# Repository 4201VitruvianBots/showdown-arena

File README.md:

SoCal Showdown Arena 
============
A field management system built around Cheesy arena with some modifications to fit the SoCal Showdown use case.

## Key features

**For participants and spectators**

* Same network isolation and security as the official FIRST FMS
* No-lag realtime scoring
* Team stack lights and seven-segment display are replaced by an LCD screen, which shows team info before the match and
  realtime scoring and timer during the match
* Smooth-scrolling rankings display
* Direct publishing of schedule, results, and rankings to The Blue Alliance

**For scorekeepers and event staff**

* Runs on Windows, macOS, and Linux
* No install prerequisites
* No "pre-start" &ndash; hardware is configured automatically and in the background
* Flexible and quick match schedule generation
* Streamlined realtime score entry
* Reports, results, and logs can be viewed from any computer
* An arbitrary number of auxiliary displays can be set up using any computer with just a web browser, to show rankings,
  queueing, field status, etc.

## License

Teams may use Cheesy Arena freely for practice, scrimmages, and off-season events. See [LICENSE](LICENSE) for more
details.

## Installing

**From a pre-built release**

Download the [latest release](https://github.com/Team254/cheesy-arena/releases). Pre-built packages are available for
Linux, macOS (x64 and M1), and Windows.

On recent versions of macOS, you may be prevented from running an app from an unidentified developer;
see [these instructions](https://support.apple.com/guide/mac-help/open-a-mac-app-from-an-unidentified-developer-mh40616/mac)
on how to bypass the warning.

**From source**

1. Download [Go](https://golang.org/dl/) (version 1.22 or later required)
1. Clone this GitHub repository to a location of your choice
1. Navigate to the repository's directory in the terminal
1. Compile the code with `go build`
1. Run the `cheesy-arena` or `cheesy-arena.exe` binary
1. Navigate to http://localhost:8080 in your browser (Google Chrome recommended)

**IP address configuration**

When running Cheesy Arena on a playing field with robots, set the IP address of the computer running Cheesy Arena to
10.0.100.5. By a convention baked into the FRC Driver Station software, driver stations will broadcast their presence on
the network to this hardcoded address so that the FMS does not need to discover them by some other method.

When running Cheesy Arena without robots for testing or development, pass the `-dev` flag to bind driver station
listeners to any local IP address.

## Network Switch

The SoCal Showdown rack contains a Cisco 3560G 48 port POE switch. This switch is really old and as a result, it needs to be configured over serial.

This can be acomplished by the following:

```
sudo yum install tftp-server
```

```bash
minicom -b 9600 -D /dev/ttyUSB0
```

Where `/dev/ttyUSB0` is the device name of the USB to serial adapter connected to the console port on the back of the switch.

To configure the switch:

```
enable
```

Then enter the switch password. To backup the configuration on the switch to a TFTP server:

```
copy startup-config tftp:
```

Then, to replace the configuration on the switch with one from the TFTP server.

```
copy tftp: startup-config
```

Finally, the configuration can be applied.

```
reload
```

Note: Use "no" when asked if you want to apply changes from running config.

## Under the hood

Cheesy Arena is written using [Go](https://golang.org), a language developed by Google and first released in 2009. Go
excels in the areas of concurrency, networking, performance, and portability, which makes it ideal for a field
management system.

Cheesy Arena is implemented as a web server, with all human interaction done via browser. The graphical interfaces are
implemented in HTML, JavaScript, and CSS. There are many advantages to this approach &ndash; development of new
graphical elements is rapid, and no software needs to be installed other than on the server. Client web pages send
commands and receive updates using WebSockets.

[Bolt](https://github.com/etcd-io/bbolt) is used as the datastore, and making backups or transferring data from one
installation to another is as simple as copying the database file.

Schedule generation is fast because pre-generated schedules are included with the code. Each schedule contains a certain
number of matches per team for placeholder teams 1 through N, so generating the actual match schedule becomes a simple
exercise in permuting the mapping of real teams to placeholder teams. The pre-generated schedules are checked into this
repository and can be vetted in advance of any events for deviations from the randomness (and other) requirements.

Cheesy Arena includes support for, but doesn't require, networking hardware similar to that used in official FRC events.
Teams are issued their own SSIDs and WPA keys, and when connected to Cheesy Arena are isolated to a VLAN which prevents
any communication other than between the driver station, robot, and event server. The network hardware is reconfigured
via SSH and Telnet commands for the new set of teams when each mach is loaded.

## PLC integration

Cheesy Arena has the ability to integrate with an Allen-Bradley PLC setup similar to the one that FIRST uses, to read
field sensors and control lights and motors. The PLC hardware travels with the FIRST California fields; contact your FTA
for more information.

The PLC code can be found [here](https://github.com/ejordan376/Cheesy-PLC).

## Team Sign integration

Cheesy Arena has the ability to integrate with
the [Cypress Team Signs](https://cypressintegration.com/customsolutions/teamdisplay/) used at official FRC events. See
the [Configuring Cheesy Arena wiki page](https://github.com/Team254/cheesy-arena/wiki/Configuring-Cheesy-Arena-Settings#team-signs)
for details configurating the team signs in Cheesy Arena.

## LED hardware

Due to the prohibitive cost of the LEDs and LED controllers used on official fields, for years in which LEDs are
mandatory for a proper game experience (such as 2018), Cheesy Arena integrates
with [Advatek](https://www.advateklights.com) controllers and LEDs.

## Advanced networking

See the [Advanced Networking wiki page](https://github.com/Team254/cheesy-arena/wiki/Advanced-Networking-Concepts) for
instructions on what equipment to obtain and how to configure it in order to support advanced network security.

## Port Configuration

| Device                       | IP Address  | Notes              |
| ---------------------------- | ----------- | ------------------ |
| FMS Computer                 | 10.0.100.5  | Gateway: 255.0.0.0 |
| Blue Alliance Station Switch | 10.0.100.62 |                    |
|                              |             |                    |

## Contributing

Cheesy Arena is far from finished! You can help by:

* Writing a missing feature, and sending a pull request
* Filing any bugs or feature requests using the [issue tracker](https://github.com/Team254/cheesy-arena/issues)
* Contributing documentation to the [wiki](https://github.com/Team254/cheesy-arena/wiki)
* Sending baked goods to [Pat](https://github.com/patfair)

## Acknowledgements

[Several folks](https://github.com/Team254/cheesy-arena/graphs/contributors) have contributed pull requests. Thanks!

In addition, the following individuals have contributed to make Cheesy Arena a reality:

* Tom Bottiglieri
* James Cerar
* Kiet Chau
* Travis Covington
* Nick Eyre
* Patrick Fairbank
* Eugene Fang
* Thad House
* Ed Jordan
* Karthik Kanagasabapathy
* Ken Mitchell
* Andrew Nabors
* Jared Russell
* Ken Schenke
* Austin Schuh
* Colin Wilson

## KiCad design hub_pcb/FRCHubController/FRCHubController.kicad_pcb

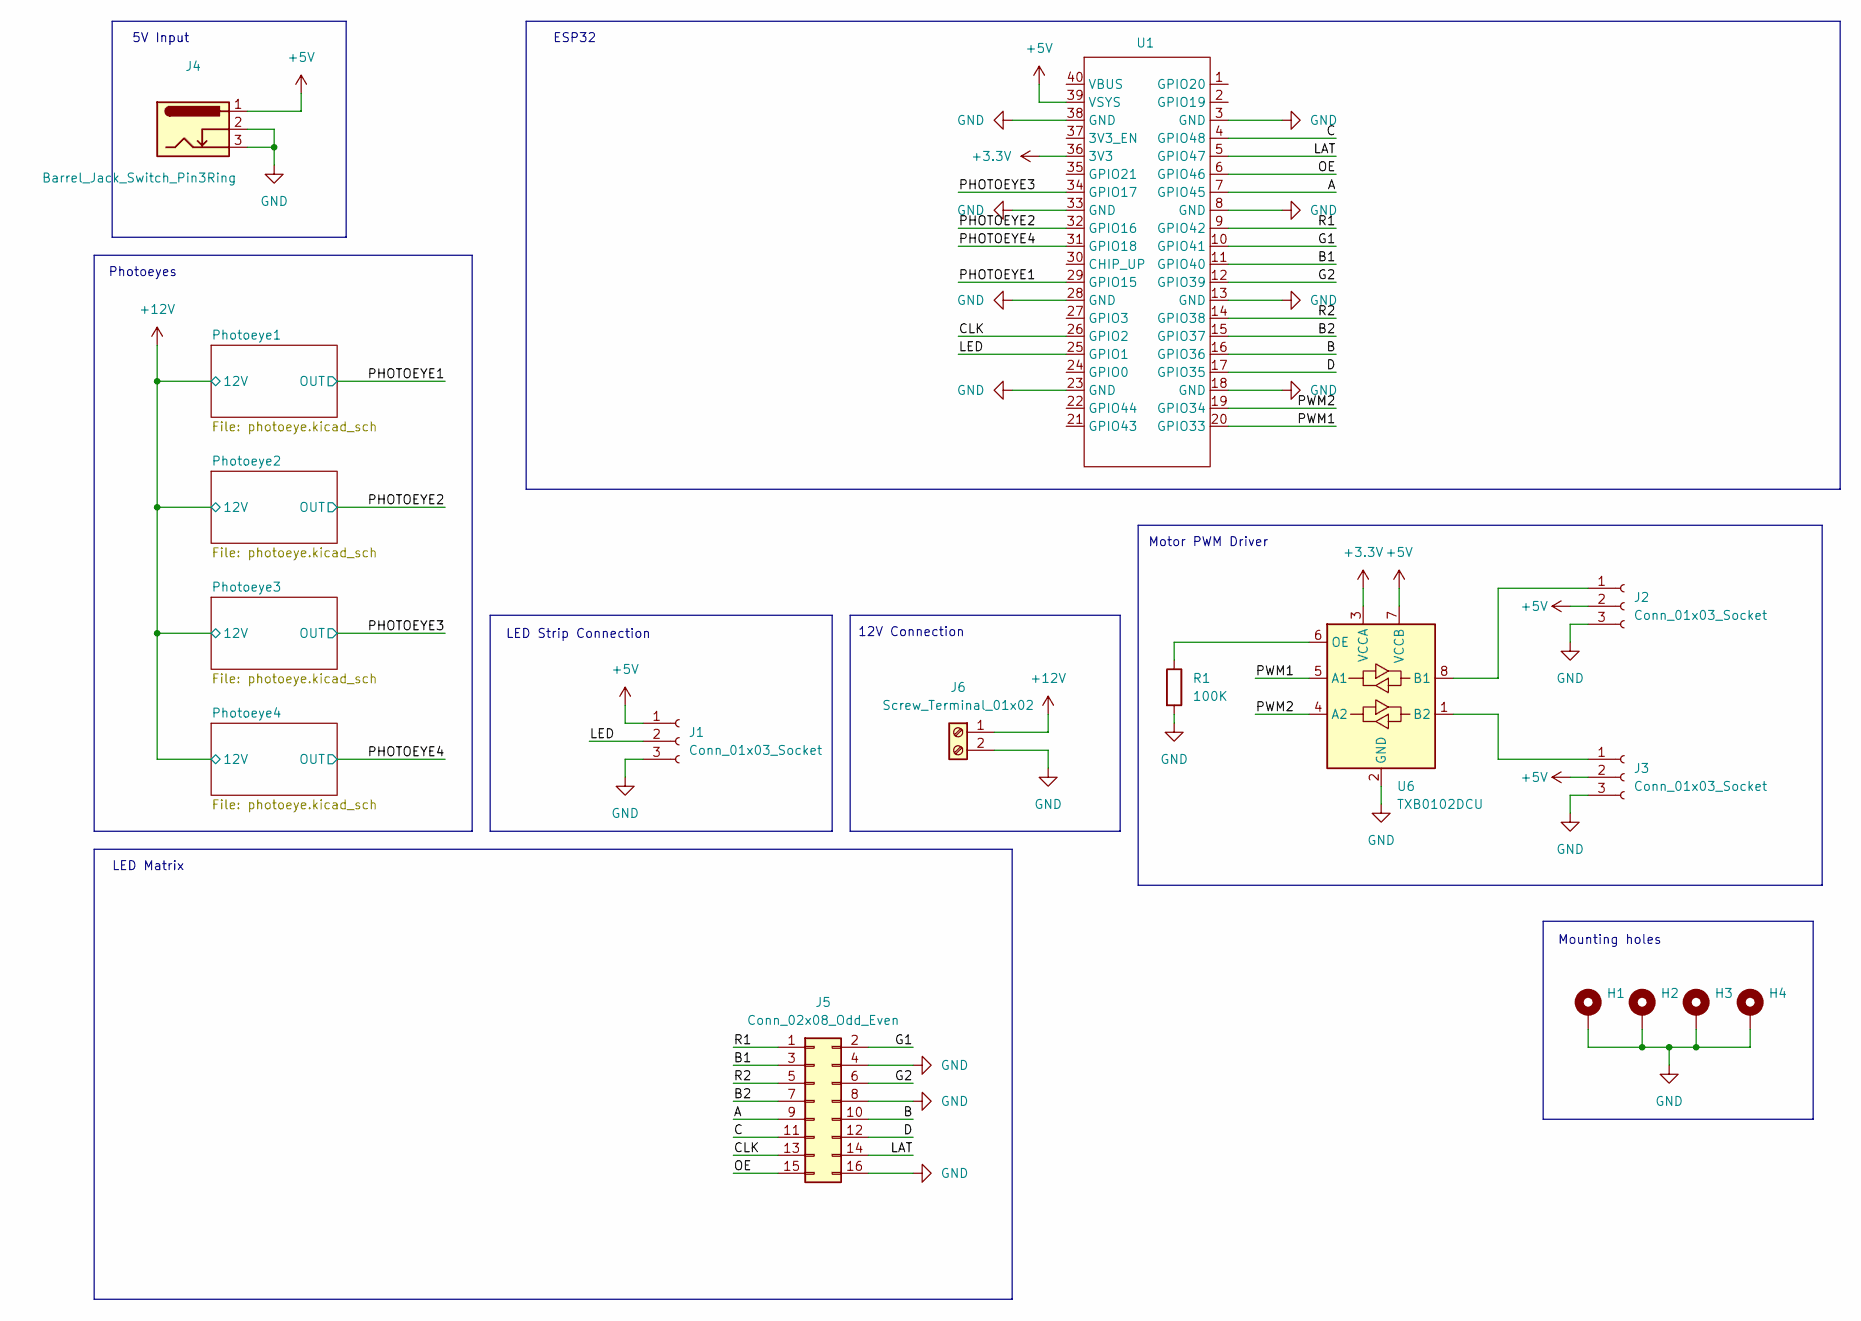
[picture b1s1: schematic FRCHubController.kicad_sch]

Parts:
H1, H2, H3, H4: MountingHole_Pad; MountingHole_5.3mm_M5_Pad
J1: Conn_01x03_Socket; JST_XH_B3B-XH-A_1x03_P2.50mm_Vertical
J2, J3: Conn_01x03_Socket; PinHeader_1x03_P2.54mm_Vertical
J4: Barrel_Jack_Switch_Pin3Ring; BarrelJack_GCT_DCJ200-10-A_Horizontal
J5: Conn_02x08_Odd_Even; PinHeader_2x08_P2.54mm_Vertical
J6: Screw_Terminal_01x02; TE_282815-2
R1: 100K; R_0603_1608Metric_Pad0.98x0.95mm_HandSolder
U1: ESP32-S3-ETH
U6: TXB0102DCU; VSSOP-8_2.3x2mm_P0.5mm

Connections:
+3.3V: U1.36 (3V3), U6.3 (VCCA)
+5V: J1.1, J2.2, J3.2, J4.1, U1.39 (VSYS), U6.7 (VCCB)
+12V: J6.1; also elsewhere on the board
/A: J5.9, U1.7 (GPIO45)
/B: J5.10, U1.16 (GPIO36)
/B1: J5.3, U1.11 (GPIO40)
/B2: J5.7, U1.15 (GPIO37)
/C: J5.11, U1.4 (GPIO48)
/CLK: J5.13, U1.26 (GPIO2)
/D: J5.12, U1.17 (GPIO35)
/G1: J5.2, U1.10 (GPIO41)
/G2: J5.6, U1.12 (GPIO39)
/LAT: J5.14, U1.5 (GPIO47)
/LED: J1.2, U1.25 (GPIO1)
/OE: J5.15, U1.6 (GPIO46)
/PHOTOEYE1: U1.29 (GPIO15); also elsewhere on the board
/PHOTOEYE2: U1.32 (GPIO16); also elsewhere on the board
/PHOTOEYE3: U1.34 (GPIO17); also elsewhere on the board
/PHOTOEYE4: U1.31 (GPIO18); also elsewhere on the board
/PWM1: U1.20 (GPIO33), U6.5 (A1)
/PWM2: U1.19 (GPIO34), U6.4 (A2)
/R1: J5.1, U1.9 (GPIO42)
/R2: J5.5, U1.14 (GPIO38)
GND: H1.1, H2.1, H3.1, H4.1, J1.3, J2.3, J3.3, J4.2, J4.3, J5.4, J5.8, J5.16, J6.2, R1.2, U1.3 (GND), U1.8 (GND), U1.13 (GND), U1.18 (GND), U1.23 (GND), U1.28 (GND), U1.33 (GND), U1.38 (GND), U6.2 (GND); also elsewhere on the board
unnamed: J2.1, U6.8 (B1)
unnamed: J3.1, U6.1 (B2)
unnamed: R1.1, U6.6 (OE)

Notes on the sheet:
LED Matrix
LED Strip Connection
Motor PWM Driver
5V Input
Mounting holes
12V Connection
ESP32
Photoeyes

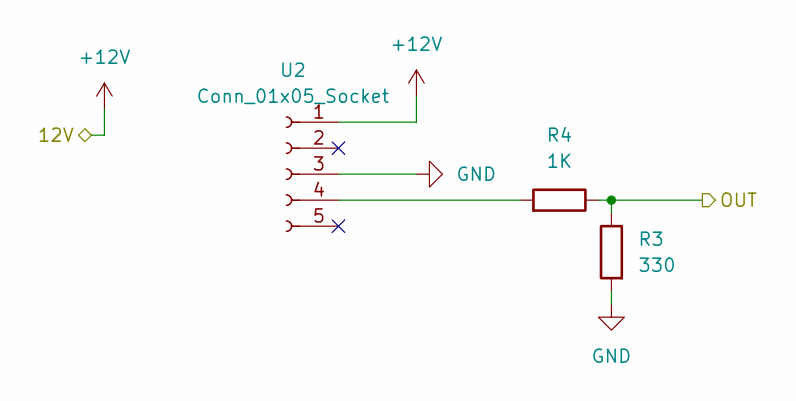
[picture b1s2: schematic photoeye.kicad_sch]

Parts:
R3: 330; R_0603_1608Metric_Pad0.98x0.95mm_HandSolder
R4: 1K; R_0603_1608Metric_Pad0.98x0.95mm_HandSolder
U2: Conn_01x05_Socket; M12

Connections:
+12V: U2.1; also elsewhere on the board
/PHOTOEYE1: R3.1, R4.1; also elsewhere on the board
GND: R3.2, U2.3; also elsewhere on the board
unnamed: R4.2, U2.4

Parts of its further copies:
R5, R7, R9: 330; R_0603_1608Metric_Pad0.98x0.95mm_HandSolder
R6, R8, R10: 1K; R_0603_1608Metric_Pad0.98x0.95mm_HandSolder
U3, U4, U5: Conn_01x05_Socket; M12

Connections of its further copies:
+12V: U3.1, U4.1, U5.1; also elsewhere on the board
/PHOTOEYE2: R5.1, R6.1; also elsewhere on the board
/PHOTOEYE3: R7.1, R8.1; also elsewhere on the board
/PHOTOEYE4: R9.1, R10.1; also elsewhere on the board
GND: R5.2, R7.2, R9.2, U3.3, U4.3, U5.3; also elsewhere on the board
unnamed: R6.2, U3.4
unnamed: R8.2, U4.4
unnamed: R10.2, U5.4

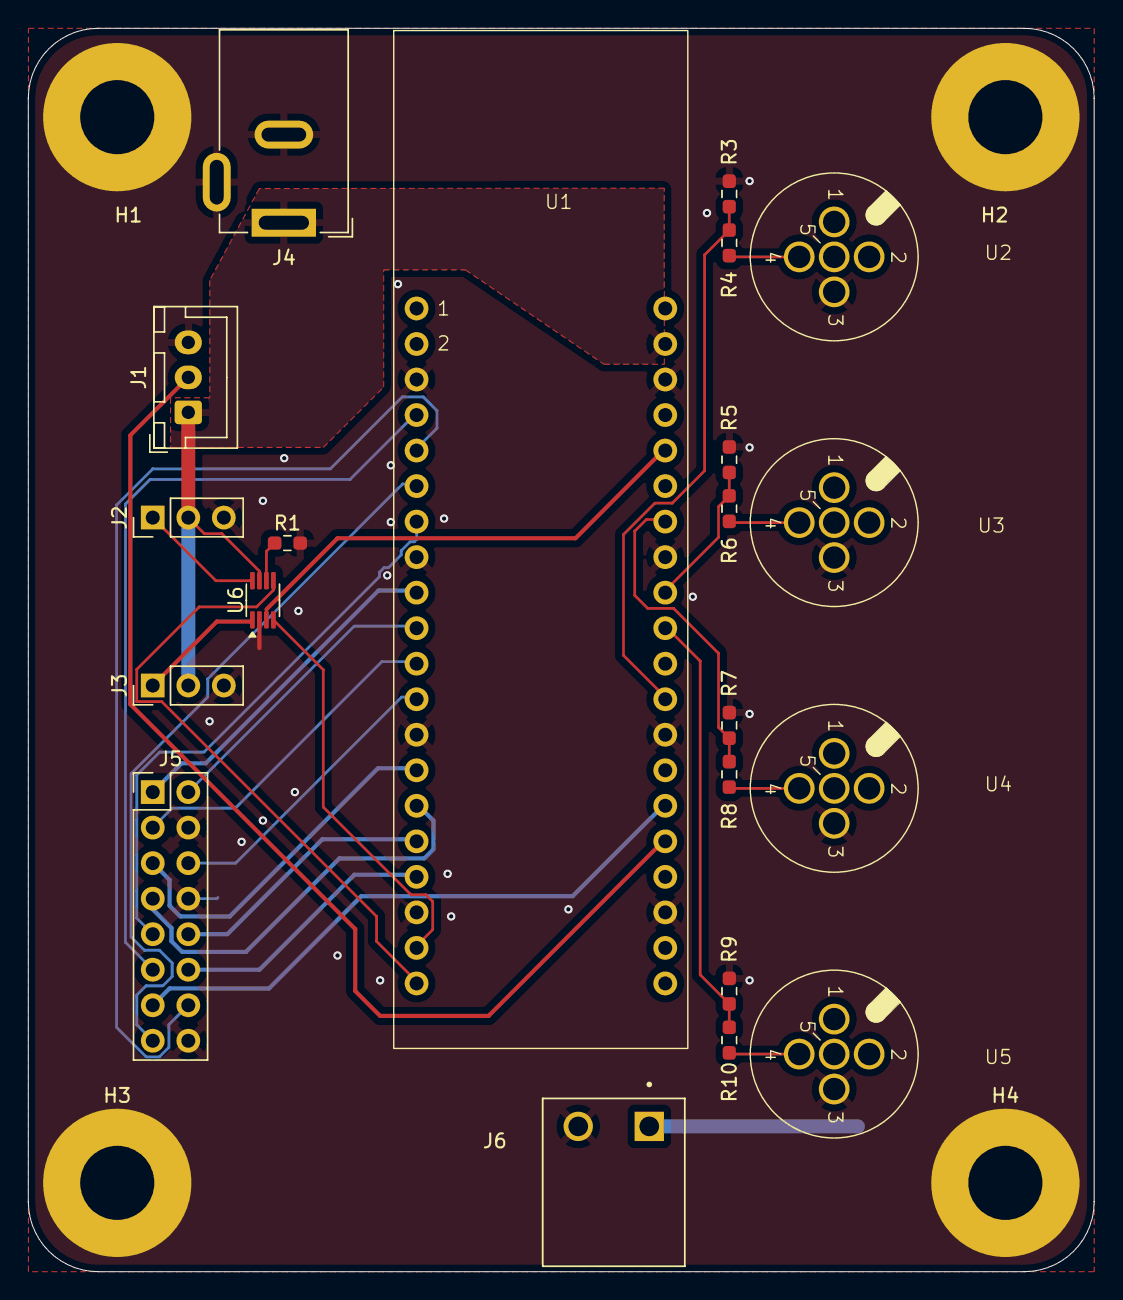
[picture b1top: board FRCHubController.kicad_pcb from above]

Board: 2 copper layers, 76.2 x 88.9 mm, 25 parts (0 on the bottom side), 31 nets.

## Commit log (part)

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2025-09-20 Removed old game logo
2025-09-22 Fixed missing Field Display Updateas
2025-09-23 Update switch configuration to not set dns server (8.8.8.8 is blocked by DaVinci wifi) and also change password and hostname
2025-09-27 Update switch config to use showdown password and add switch instructions to readme
2025-09-27 Make background of audience display transparent
2025-09-27 Tweak colors and backgrounds and logos
2025-09-27 Adds support for Bitfocus Companion Closes #211
2025-09-27 Add estops
2025-10-01 Make it so that FTA display also plays sounds (required as field uses FTA display PI to supply match sounds)
2025-10-01 Clean up estops code
2025-10-05 Revert "Clean up estops code"
    This reverts commit 91c7ae595d879f7751e125834daf2719982a5f49.
2025-10-06 Add field break after match 12
2025-10-08 Remove extraneous break after testing
2025-10-10 Hybrid IO setup
2025-11-08 Add hacked files for FLL
2025-11-08 Hacks from SoCal Showdown 2025
2026-01-26 Bring estops from socal showdown 2025
2026-01-26 Add requirements.txt
2026-01-26 add in shooter hub project
2026-01-26 Add in app_scoring
2026-02-02 Add in shooter hub prelim software
2026-02-06 Add hub scorer PCB
2026-02-07 Layout PCB
2026-02-09 Update layout
2026-02-11 Complete layout
2026-02-18 Update pinmaps
2026-02-18 Small tweaks to make scoring more reliable
2026-02-21 In progress matrix updates
2026-02-22 fix text centering
2026-03-01 Final Hub PCBA + other things
2026-03-04 Bunch more changes
2026-03-04 Bunch more things
2026-03-07 Fix PWM
